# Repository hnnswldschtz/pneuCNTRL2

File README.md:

# pneuCNTRL2 Firmware
8 channel pressure controlled inlation/deflation system for the inflatable haptics experiments

Setup:

- custom PCB released as openhardware under cern-ohl-w v2 license
- based on teensy3.2
- ads1115 for ADC
- MCP4728 for DAC
- 4x festo 571482 pressure sensors
- 4x smc 5/3 electric valves
- 4x Festo proportional piezo valves (VEAB-L-26-D7-Q4-V1-1R1)
- LCD i2c display

libraries used:
ADS1115_lite: https://github.com/terryjmyers/ADS1115-Lite
Adafruit_MCP4728: https://github.com/adafruit/Adafruit_MCP4728
Adafruit_NeoPixel: https://github.com/adafruit/Adafruit_NeoPixel
LiquidCrystal_I2C: https://github.com/johnrickman/LiquidCrystal_I2C -> this gives a massive delay when used! maybe avoid!!
Adafruit_ADS1015: https://github.com/adafruit/Adafruit_ADS1X15

Bauhaus-University Weimar \
hnns 2022

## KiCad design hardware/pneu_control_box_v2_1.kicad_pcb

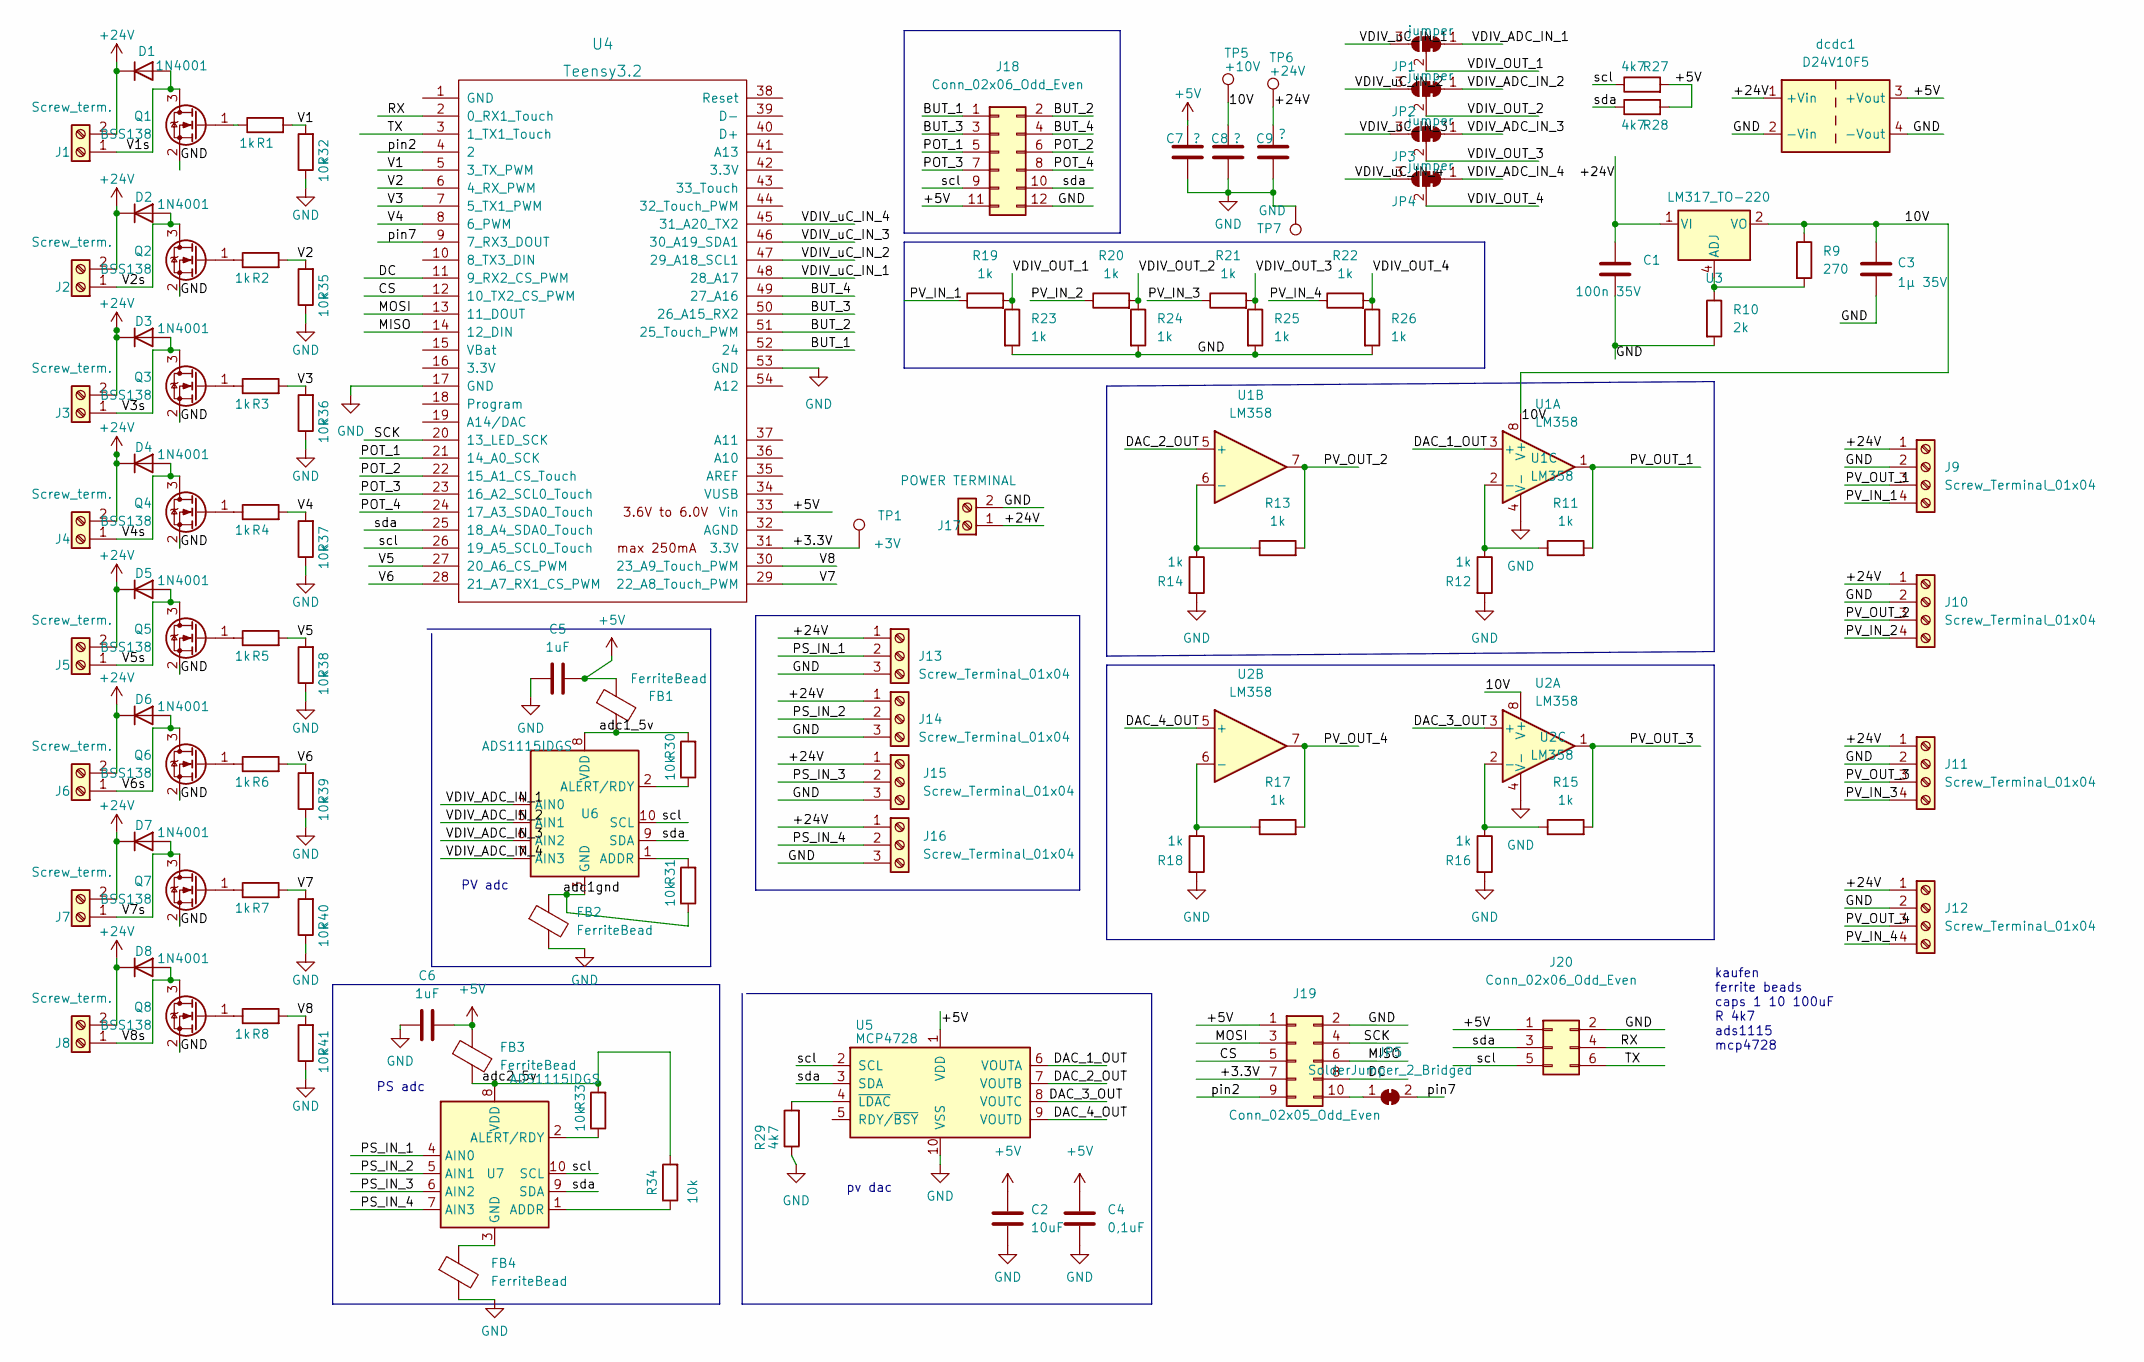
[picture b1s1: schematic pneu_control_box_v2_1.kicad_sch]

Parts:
C1: 100n 35V; C_1206_3216Metric
C2: 10uF; C_1206_3216Metric
C3: 1µ 35V; C_1206_3216Metric
C4: 0,1uF; C_1206_3216Metric
C5, C6: 1uF; C_1206_3216Metric
C7, C8, C9: ?; C_1206_3216Metric
D1, D2, D3, D4, D5, D6, D7, D8: 1N4001; D_SMA
FB1, FB2, FB3, FB4: FerriteBead; C_0805_2012Metric_Pad1.18x1.45mm_HandSolder
J1, J2, J3, J4, J5, J6, J7, J8: Screw_term.; TerminalBlock_Phoenix_MKDS-1,5-2_1x02_P5.00mm_Horizontal
J9, J10, J11, J12: Screw_Terminal_01x04; TerminalBlock_Phoenix_MKDS-1,5-4_1x04_P5.00mm_Horizontal
J13, J14, J15, J16: Screw_Terminal_01x04; TerminalBlock_Phoenix_MKDS-1,5-3_1x03_P5.00mm_Horizontal
J17: POWER TERMINAL; TerminalBlock_Phoenix_MKDS-1,5-2_1x02_P5.00mm_Horizontal
J18: Conn_02x06_Odd_Even; IDC-Header_2x06_P2.54mm_Vertical
J19: Conn_02x05_Odd_Even; IDC-Header_2x05_P2.54mm_Vertical
J20: Conn_02x06_Odd_Even; IDC-Header_2x03_P2.54mm_Vertical
JP1, JP2, JP3, JP4: jumper; SolderJumper-3_P1.3mm_Bridged12_Pad1.0x1.5mm
JP5: SolderJumper_2_Bridged; SolderJumper-2_P1.3mm_Bridged2Bar_Pad1.0x1.5mm
Q1, Q2, Q3, Q4, Q5, Q6, Q7, Q8: BSS138; SOT-23
R1, R2, R3, R4, R5, R6, R7, R8, R11, R12, R13, R14, R15, R16, R17, R18, R19, R20, R21, R22, R23, R24, R25, R26: 1k; R_0805_2012Metric_Pad1.20x1.40mm_HandSolder
R9: 270; R_0805_2012Metric_Pad1.20x1.40mm_HandSolder
R10: 2k; R_0805_2012Metric_Pad1.20x1.40mm_HandSolder
R27, R28, R29: 4k7; R_0805_2012Metric_Pad1.20x1.40mm_HandSolder
R30, R31, R32, R33, R34, R35, R36, R37, R38, R39, R40, R41: 10k; R_0805_2012Metric_Pad1.20x1.40mm_HandSolder
TP1: +3V; Pin_D1.0mm_L10.0mm
TP5: +10V; Pin_D1.0mm_L10.0mm
TP6: +24V; Pin_D1.0mm_L10.0mm
TP7: GND; Pin_D1.0mm_L10.0mm
U1, U2: LM358; SOIC-8_3.9x4.9mm_P1.27mm
U3: LM317_TO-220; SOIC-8_3.9x4.9mm_P1.27mm
U4: Teensy3.2; Teensy30_31_32_All_Pins
U5: MCP4728; MSOP-10_3x3mm_P0.5mm
U6, U7: ADS1115IDGS; TSSOP-10_3x3mm_P0.5mm
dcdc1: D24V10F5; LM2596 DC-DC

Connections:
+5V: C2.1, C4.1, C5.2, C6.2, C7.1, FB1.1, FB3.1, J18.11, J19.1, J20.1, R27.2, R28.2, U4.33 (Vin), U5.1 (VDD), dcdc1.3 (+Vout)
+24V: C1.1, C9.1, D1.1 (K), D2.1 (K), D3.1 (K), D4.1 (K), D5.1 (K), D6.1 (K), D7.1 (K), D8.1 (K), J1.2, J2.2, J3.2, J4.2, J5.2, J6.2, J7.2, J8.2, J9.1, J10.1, J11.1, J12.1, J13.1, J14.1, J15.1, J16.1, J17.1, TP6.1, U3.1 (VI), dcdc1.1 (+Vin); also elsewhere on the board
/10V: C3.1, C8.1, R9.1, TP5.1, U1.8 (V+), U2.8 (V+), U3.2 (VO), U3.3 (VI), U3.6 (VI), U3.7 (VI); also elsewhere on the board
/+3.3V: J19.7, TP1.1, U4.31 (3.3V); also elsewhere on the board
/BUT_1: J18.1, U4.52 (24)
/BUT_2: J18.2, U4.51 (25_Touch_PWM)
/BUT_3: J18.3, U4.50 (26_A15_RX2)
/BUT_4: J18.4, U4.49 (27_A16)
/CS: J19.5, U4.12 (10_TX2_CS_PWM)
/DAC_1_OUT: U1.3 (+), U5.6 (VOUTA)
/DAC_2_OUT: U1.5 (+), U5.7 (VOUTB)
/DAC_3_OUT: U2.3 (+), U5.8 (VOUTC)
/DAC_4_OUT: U2.5 (+), U5.9 (VOUTD)
/DC: J19.8, U4.11 (9_RX2_CS_PWM)
/MISO: J19.6, U4.14 (12_DIN)
/MOSI: J19.3, U4.13 (11_DOUT)
/POT_1: J18.5, U4.21 (14_A0_SCK)
/POT_2: J18.6, U4.22 (15_A1_CS_Touch)
/POT_3: J18.7, U4.23 (16_A2_SCL0_Touch)
/POT_4: J18.8, U4.24 (17_A3_SDA0_Touch)
/PS_IN_1: J13.2, U7.4 (AIN0)
/PS_IN_2: J14.2, U7.5 (AIN1)
/PS_IN_3: J15.2, U7.6 (AIN2)
/PS_IN_4: J16.2, U7.7 (AIN3)
/PV_IN_1: J9.4, R19.1
/PV_IN_2: J10.4, R20.1
/PV_IN_3: J11.4, R21.1
/PV_IN_4: J12.4, R22.1
/PV_OUT_1: J9.3, R11.2, U1.1
/PV_OUT_2: J10.3, R13.2, U1.7
/PV_OUT_3: J11.3, R15.2, U2.1
/PV_OUT_4: J12.3, R17.2, U2.7
/RX: J20.4, U4.2 (0_RX1_Touch)
/SCK: J19.4, U4.20 (13_LED_SCK)
/TX: J20.6, U4.3 (1_TX1_Touch)
/V1: R1.2, R32.2, U4.5 (3_TX_PWM)
/V1s: D1.2 (A), J1.1, Q1.3 (D)
/V2: R2.2, R35.2, U4.6 (4_RX_PWM)
/V2s: D2.2 (A), J2.1, Q2.3 (D)
/V3: R3.2, R36.2, U4.7 (5_TX1_PWM)
/V3s: D3.2 (A), J3.1, Q3.3 (D)
/V4: R4.2, R37.2, U4.8 (6_PWM)
/V4s: D4.2 (A), J4.1, Q4.3 (D)
/V5: R5.2, R38.2, U4.27 (20_A6_CS_PWM)
/V5s: D5.2 (A), J5.1, Q5.3 (D)
/V6: R6.2, R39.2, U4.28 (21_A7_RX1_CS_PWM)
/V6s: D6.2 (A), J6.1, Q6.3 (D)
/V7: R7.2, R40.2, U4.29 (22_A8_Touch_PWM)
/V7s: D7.2 (A), J7.1, Q7.3 (D)
/V8: R8.2, R41.2, U4.30 (23_A9_Touch_PWM)
/V8s: D8.2 (A), J8.1, Q8.3 (D)
/VDIV_ADC_IN_1: JP1.1 (A), U6.4 (AIN0)
/VDIV_ADC_IN_2: JP2.1 (A), U6.5 (AIN1)
/VDIV_ADC_IN_3: JP3.1 (A), U6.6 (AIN2)
/VDIV_ADC_IN_4: JP4.1 (A), U6.7 (AIN3)
/VDIV_OUT_1: JP1.2 (C), R19.2, R23.1
/VDIV_OUT_2: JP2.2 (C), R20.2, R24.1
/VDIV_OUT_3: JP3.2 (C), R21.2, R25.1
/VDIV_OUT_4: JP4.2 (C), R22.2, R26.1
/VDIV_uC_IN_1: JP1.3 (B), U4.48 (28_A17)
/VDIV_uC_IN_2: JP2.3 (B), U4.47 (29_A18_SCL1)
/VDIV_uC_IN_3: JP3.3 (B), U4.46 (30_A19_SDA1)
/VDIV_uC_IN_4: JP4.3 (B), U4.45 (31_A20_TX2)
/adc1_5v: FB1.2, R30.2, U6.8 (VDD)
/adc1gnd: FB2.1, R31.1, U6.3 (GND)
/adc2_5v: FB3.2, R33.2, R34.2, U7.8 (VDD)
/pin2: J19.9, U4.4 (2)
/pin7: JP5.2 (B), U4.9 (7_RX3_DOUT)
/scl: J18.9, J20.5, R27.1, U4.26 (19_A5_SCL0_Touch), U5.2 (SCL), U6.10 (SCL), U7.10 (SCL)
/sda: J18.10, J20.3, R28.1, U4.25 (18_A4_SDA0_Touch), U5.3 (SDA), U6.9 (SDA), U7.9 (SDA)
GND: C1.2, C2.2, C3.2, C4.2, C5.1, C6.1, C7.2, C8.2, C9.2, FB2.2, FB4.2, J9.2, J10.2, J11.2, J12.2, J13.3, J14.3, J15.3, J16.3, J17.2, J18.12, J19.2, J20.2, Q1.2 (S), Q2.2 (S), Q3.2 (S), Q4.2 (S), Q5.2 (S), Q6.2 (S), Q7.2 (S), Q8.2 (S), R10.2, R12.2, R14.2, R16.2, R18.2, R23.2, R24.2, R25.2, R26.2, R29.1, R32.1, R35.1, R36.1, R37.1, R38.1, R39.1, R40.1, R41.1, TP7.1, U1.4 (V-), U2.4 (V-), U4.17 (GND), U4.53 (GND), U5.10 (VSS), dcdc1.2 (-Vin), dcdc1.4 (-Vout); also elsewhere on the board
unnamed: FB4.1, U7.3 (GND)
unnamed 72: J19.10, JP5.1 (A); also elsewhere on the board
unnamed: Q1.1 (G), R1.1
unnamed: Q2.1 (G), R2.1
unnamed: Q3.1 (G), R3.1
unnamed: Q4.1 (G), R4.1
unnamed: Q5.1 (G), R5.1
unnamed: Q6.1 (G), R6.1
unnamed: Q7.1 (G), R7.1
unnamed: Q8.1 (G), R8.1
unnamed: R9.2, R10.1, U3.4 (ADJ)
unnamed: R11.1, R12.1, U1.2 (-)
unnamed: R13.1, R14.1, U1.6 (-)
unnamed: R15.1, R16.1, U2.2 (-)
unnamed: R17.1, R18.1, U2.6 (-)
unnamed: R29.2, U5.4 (~LDAC)
unnamed: R30.1, U6.2 (ALERT/RDY)
unnamed: R31.2, U6.1 (ADDR)
unnamed: R33.1, U7.2 (ALERT/RDY)
unnamed: R34.1, U7.1 (ADDR)

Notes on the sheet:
kaufen ferrite beads caps 1 10 100uF R 4k7 ads1115 mcp4728
PS adc
pv dac
PV adc

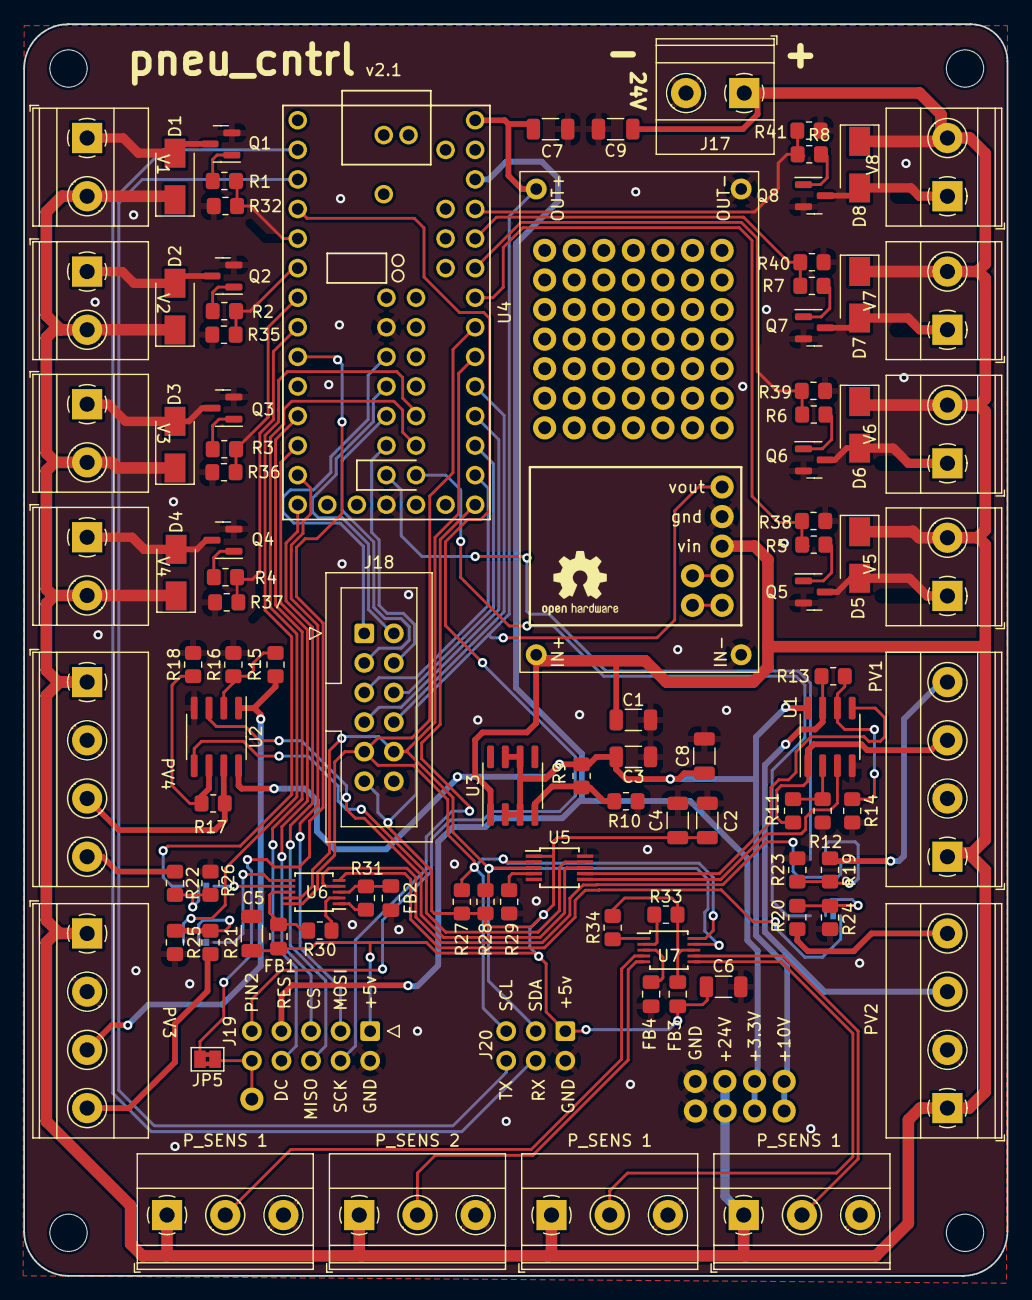
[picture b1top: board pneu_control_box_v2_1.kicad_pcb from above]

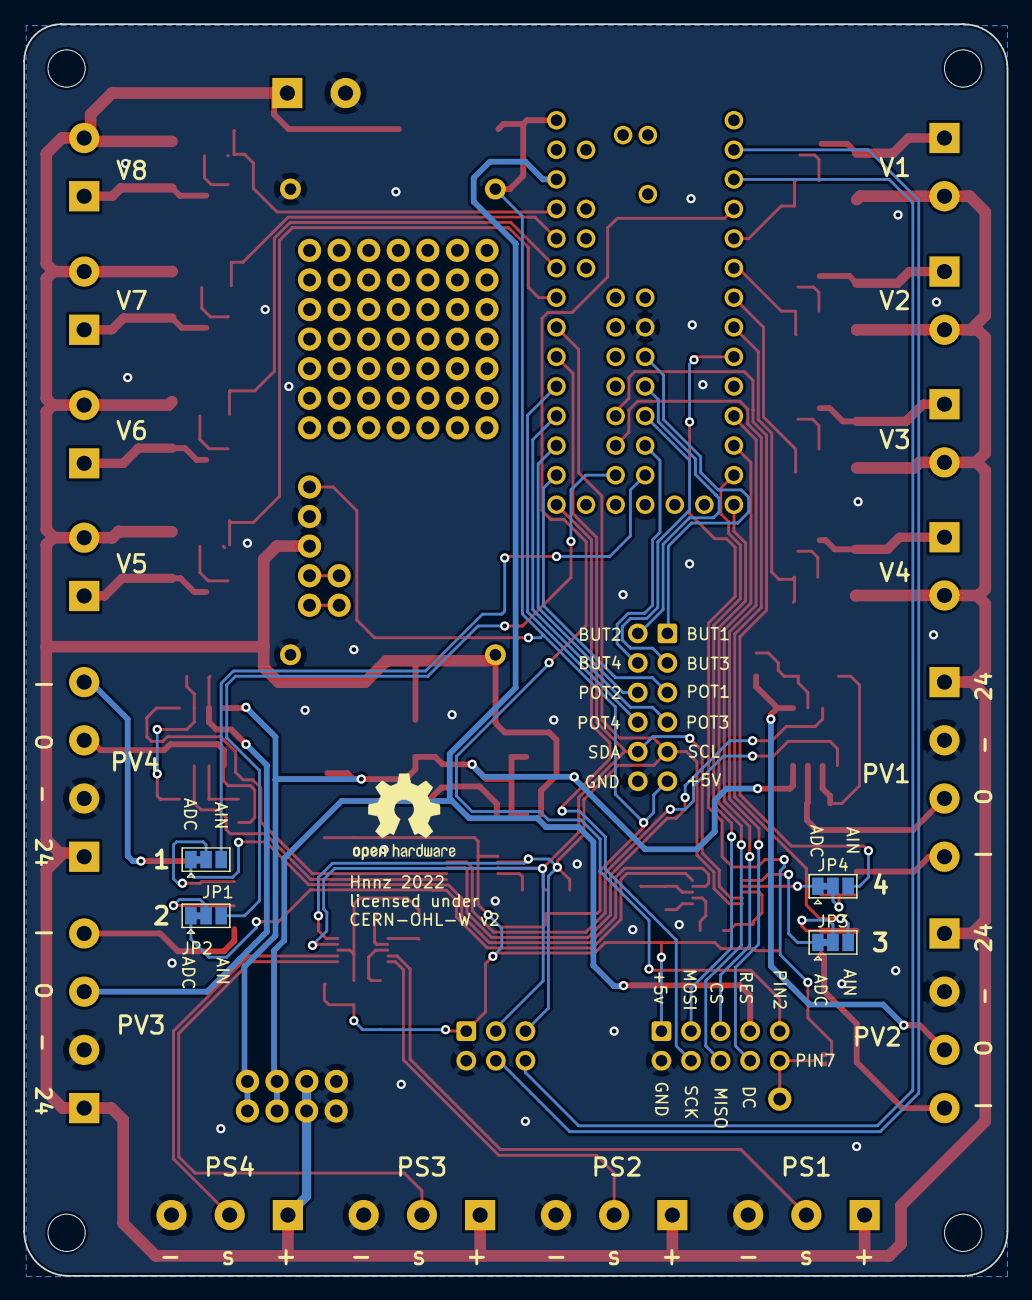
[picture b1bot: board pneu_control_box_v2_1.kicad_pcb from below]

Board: 2 copper layers, 84.5 x 107.5 mm, 166 parts (4 on the bottom side), 91 nets.

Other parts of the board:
TP6#2: +24V; Pin_D1.0mm_L10.0mm
p, p1, p2, p3, p4, p5, p6, p7, p8, p9, p10, p11, p12, p13, p14, p15, p16, p17, p18, p19, p20, p21, p22, p23, p24, p25, p26, p27, p28, p29, p30, p31, p32, p33, p34, p35, p36, p37, p38, p39, p40, p41, p42, p43, p44, p45, p46, p47, p48, p49, p50, p51, p52, p53, p54: solderPin; Pin_D1.0mm_L10.0mm
p#2, p#3, p#4: solderPin; Pin_D1.0mm_L10.0mm

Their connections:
+24V: TP6#2.1, p49.1; also elsewhere on the board
/10V: p51.1; also elsewhere on the board
/+3.3V: p50.1; also elsewhere on the board
GND: p#3.1; also elsewhere on the board
unnamed 72: p.1; also elsewhere on the board

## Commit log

2021-04-15 pushed into git
2021-04-26 sequencer mode
2021-04-26 minor typos
2022-02-18 refactor, initiation for port to new hardware
2022-04-28 refactor, try ADS1115_lite lib, user test one live code
2023-01-18 hardware
2023-01-18 OH license
2023-01-19 license
2023-06-27 library import updated
2025-06-25 update 202
2025-06-25 get setlists and output timing
2025-06-25 set mode and training mode with lists
2025-06-25 random data generation
2025-10-14 Working Study Setup Aug to Sep 2025

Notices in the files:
hardware/pneu_control_box_v2_1.kicad_pcb:
licensed under
CERN-OHL-W v2
